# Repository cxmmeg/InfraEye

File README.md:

# InfraEye
**InfraEye** is name for low cost thermal image camera project based on SoC ESP32. 

It uses IR sensor MLX90640B. Image can be viewed by default on web page on web server created by ESP32 or optionally on 2.4'' LCD touch display.

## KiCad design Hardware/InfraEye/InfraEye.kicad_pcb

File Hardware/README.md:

PCB will have ESP8266, Infra sensor, micro USB conector, DC-DC inverter and LCD

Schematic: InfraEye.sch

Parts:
C1, C3: 10nF; C_1206_5MIL_DWS_ISO
C2, C4: 100nF; C_1206_5MIL_DWS_ISO
C5, C6: CP; C_Radial_D5.0mm_H11.0mm_P2.00mm
D1, D2, D3, D4: D; D_1206_3216Metric
D5: D_Zener; D_1206_3216Metric
J1: Conn_01x03_Male; FanPinHeader_1x03_P2.54mm_Vertical
Q1: Q_NPN_BCE; SOT23-3
R1, R2: R; R_1206_5MIL_DWS_ISO
R3: R; R_1206_3216Metric
U1, U4: MLX90640; MLX90614
U2: ESP32-WROOM-32; ESP32-WROOM-32-30pin
U3: TFT_SPI_24_LCD; TFT_LCD_24
U5: LT1129-3.3_SOT223; SOT-223-3_TabPin2

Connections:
+3V3: C1.1, C2.1, C3.1, C4.1, Q1.2 (C), R3.2, U1.2 (VDD), U2.16, U3.1 (VCC), U4.2 (VDD)
+5V: C6.1, U2.1, U5.3
GND: C1.2, C2.2, C3.2, C4.2, C5.2, C6.2, D3.2, D4.1, D5.2, U1.3 (GND), U2.2, U2.17, U3.2 (GND), U4.3 (GND), U5.2
unnamed: C5.1, D1.1, D2.2, D5.1, U5.1
unnamed: D1.2, D3.1, J1.1
unnamed: D2.1, D4.2, J1.2
unnamed: Q1.1 (B), R1.1
unnamed: Q1.3 (E), R2.1
unnamed: R1.2, U2.26
unnamed: R2.2, R3.1, U3.8 (LEDD)
unnamed: U1.1 (SDA), U2.30, U4.1 (SDA)
unnamed: U1.4 (SCL), U2.29, U4.4 (SCL)
unnamed: U2.3, U3.14 (IRQT)
unnamed: U2.4, U3.11 (CST)
unnamed: U2.8, U3.10 (CLKT), U3.18 (SCKC)
unnamed: U2.9, U3.12 (MOSIT), U3.17 (MISOC)
unnamed: U2.10, U3.13 (MISO), U3.16 (MOSIC)
unnamed: U2.11, U3.9 (MISOD)
unnamed: U2.12, U3.15 (CSC)
unnamed: U2.18, U3.3 (CSD)
unnamed: U2.20, U3.4 (RSTD)
unnamed: U2.23, U3.5 (DCD)
unnamed: U2.24, U3.6 (MOSID)
unnamed: U2.25, U3.7 (SCKD)

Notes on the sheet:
Component placement legend: B - Basic components - always populated W - WIFI version L - LCD version A - AC power supply R - Relay O - LCD backlight always on
Power supply

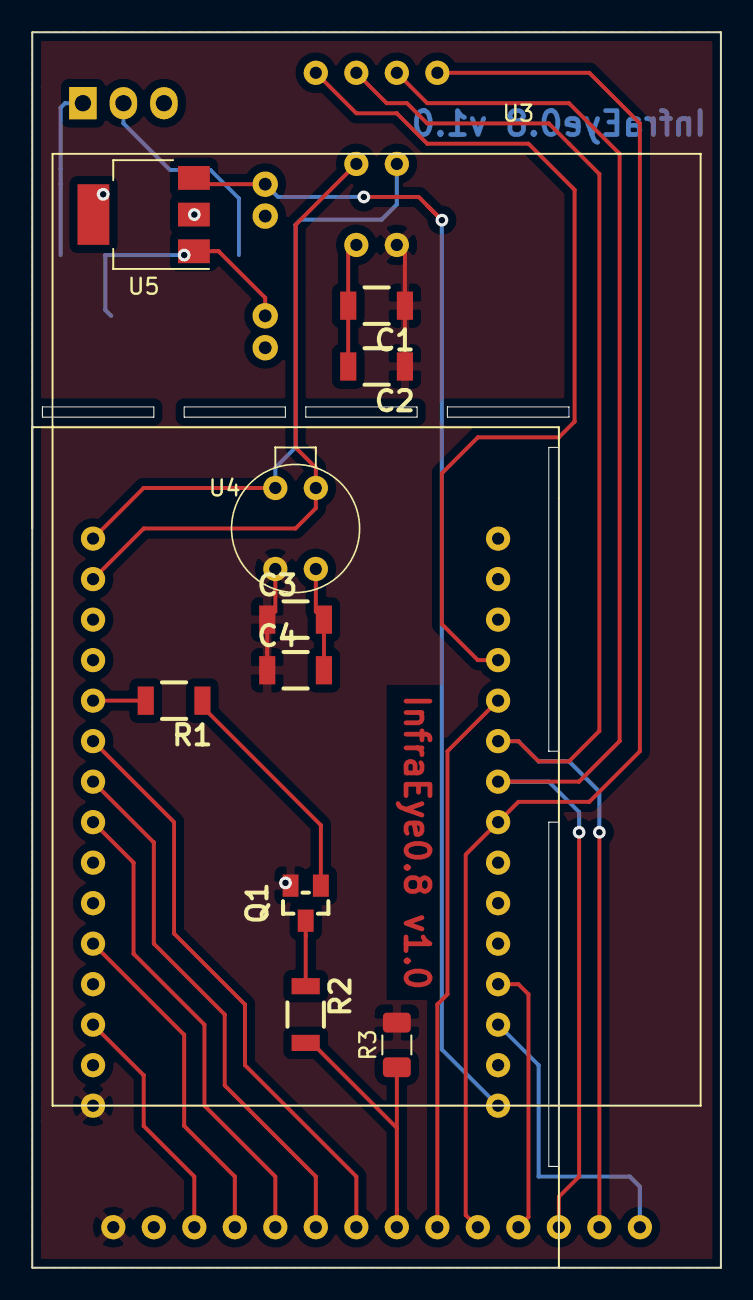
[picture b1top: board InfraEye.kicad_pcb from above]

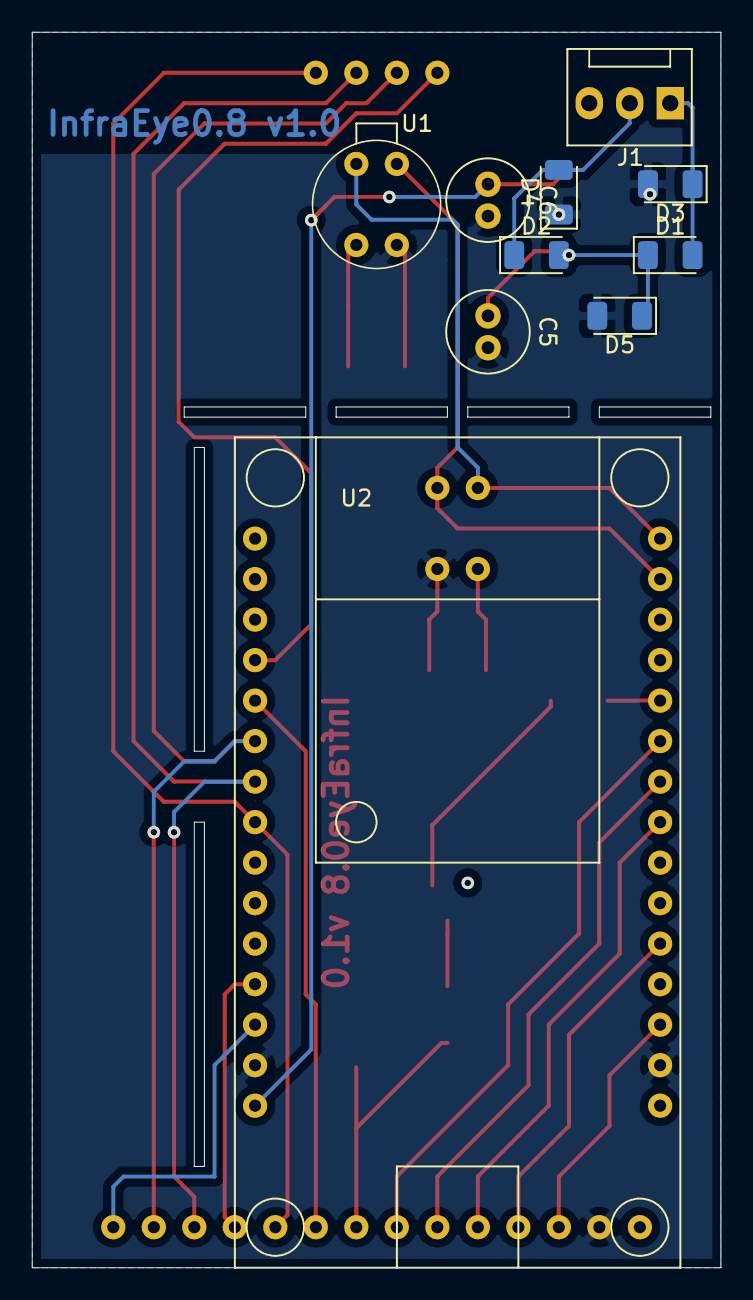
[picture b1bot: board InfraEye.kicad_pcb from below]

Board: 2 copper layers, 43.2 x 77.5 mm, 21 parts (10 on the bottom side), 24 nets.

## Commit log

2018-12-21 Created basic directory structure
2019-01-17 Create 3_Processor
2019-01-17 Create 4_Display
2019-01-17 Create 5_Enclosure
2019-02-10 First draft of Arduino source with I2C communication with IR sensor working
2019-02-10 Fixed problem with buffer length of I2C
    Arduino Wire library is using 32 byte buffer, therefore transaction longer than 32 bytes of usefull data is not possible. Modified to read in chunks not longer tan 32 bytes.
    Added reading of frame from IR sensor. Conversion to temperature added too, but not functional yet.
2019-02-10 Fixed error in I2C driver
    When more than 32 bytes was requested to be read, repeatedly first 32 bytes was read, address was not modified.
2019-02-10 Temperature reading of all pixels implemented
    Both subpages are read now, which allows for calculation of temperatures for all pixels. Correct timing has to be determined as frame rate is currently very low.
2019-02-11 Upscaling algorithm for output data from sensor created in MATLAB.
2019-02-11 Changed mapping of pins so both IR sensor and LCD work together
2019-02-11 Generated C code for upscaling algorithm added.
2019-02-11 Image is displayed on LCD
    32x24 blue coded image is deisplayed on screen
2019-02-11 Generated C code for 4x upscaling algorithm added.
2019-02-12 Generated C code for 2x upscaling algorithm added.
2019-02-12 Added "Iron" IR color palette
    IR color palette implemented
    Automatic range implemented
    Min and Max tepleratures displayed
    Size of image on LCD increased by factor of 8 (huge pixels)
2019-02-15 Improved frame rate to 4FPS
    Changed pattern to interleaved, so only changed pixels can be read efficiently.
    Also only changed pixels are overwritten on LCD.
2019-02-16 Image upscaling algorithm in C added as CodeBlocks project.
2019-02-16 Added document with pinouts and connections
2019-02-17 Image upscaling module added to project.
2019-02-17 Upscaled image displaying added.
2019-02-18 Added upScale sources
    Updated pinout documentaion
    Not a working version
2019-02-18 Revert "Merge branch 'master' of https://github.com/sifosifo/InfraEye"
    This reverts commit 87dfc76a51ad3bbe426f63e0371d4fdf24245b95, reversing
    changes made to 93dad1b0883cd35a66c8071b71e3ff332ed7278e.
2019-02-18 Original and upscaled images on LCD side by side
    Upscaled image on left side and original image at right side of LCD.
    Upscaled image is just black for now for unknown bug.
2019-02-18 Image upscaling fixed.
2019-02-18 Added LIVE_DATA flag
    LIVE_DATA not defined means that temperatures are not taken from IR sensor, but from static array
2019-02-18 Conversion function fixed.
2019-02-19 Beautifull upscaled image at 1,4FPS
2019-02-19 Picture is created only once per full frame
    Due to long calculation times, subPages get lost and picture is distorted.
2019-02-19 GetFrame time reduced by 10ms
    Time reduced from 42ms to 31ms by reading only current subPage.
2019-02-20 Fixed error in GetFrameData
    Error with missing subPages still missing.
    GetFrame now takes 22ms instead of original 42ms
2019-02-21 Fixed problem with loosing subPage 0
    Real FPS is 1 now.
    Changed algorithm to make sure no subPage is lost.
    Image processing is terminated when new subPage is ready for reading resulting in partial image in case that FPS of sensor is too high.
2019-02-21 Image processing is executed during both subPages
    Real FPS is 2
    No buffer is used to make sure that single complete frame is displayed. It is visible.
2019-02-21 Full image is always drawn
    If image processing takes longer than whole frame measurement, image processing is carried out during next frame measurement.
2019-02-22 Created modules
    New module for LCD
    New module for IRsensor
    New config file for whole project
2019-02-22 Added refresh rate of IR sensor into config file
2019-02-22 Reworked time measurement
2019-02-23 Upscaling algorithm optimalized for scaling factor 4.
2019-02-24 Changed temperatures from float to uint16_t
2019-02-24 Fixed type errors
2019-02-24 Look-up tables added.
2019-02-24 Fixed point upscaling algorithm updated. Displaying is not correct - need to be fixed.
2019-02-27 Fixed LIVE_DATA macro, updated documentation - ESP32 added
2019-03-01 LOOK_UP_TABLE_D moved to header file.
2019-04-08 Update Pinounts and connections.docx
    Added pinouts for ESP32 and LCD
2019-04-18 .gitignore added.
2019-04-18 Arduino project deleted from master branch. Arduino source code can be found in dev_arduino branch. New ESP-IDF Toolchain LED blinking application added into master branch.
2019-04-19 Build configuration guide using ESP-IDF toolchain added. Front page README.md updated.
2019-05-01 ESP-IDF display example added.
2019-05-02 app_display module reworked.
2019-05-11 Frequency switched to 240 MHz Moving rectangle application created.
2019-05-11 Removed sdkconfig as it is unique for everybody and having it in repo is causing conflicts.
2019-05-12 Added two tasks. One is currently used just for debugging and the other one makes recalculation for display. In main (idle task) LCD is updated.
2019-05-12 FPS calculation added, not sure if it's calculated correctly.
2019-06-23 For MLX90640 IR sensor added: driver and I2C driver. I2C not working yet.
2019-06-30 I2C driver is initialized and installed. i2c_master_cmd_begin() returns -1 - general I2C error, therefore I2C scan fails.
2019-07-01 I2C scan now finds IR sensor, but timeout is detected ESP_ERR_TIMEOUT 0x107 /*!< Operation timed out */
2019-07-01 I2C scan now finds IR sensor correctly
2019-07-03 I2C read function rewritten from "Arduino to esp_idf", not yet verified if correctly.
2019-07-27 Display colour setting fixed.
2019-07-27 Colour is set according to I2C status.
2019-07-27 Image upscaling module added.
2019-07-28 FPS calculation updated and added into display module. FPS is now 21.
2019-08-26 Updated I2C write. Something is still correct. Value that is read out doesn't match the one that was written. At this point it is not clear if it is issue of reading or writing. Logical analyzator co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
2019-08-27 I2C reading was not correct, repeated start was not present. Both reading and writing seems to be working correctly. Cleanup is needed and debug messages needs to be removed/commented out.
2019-08-28 When using i2c_master_read() MSB, LSB are swapped in every word. When using i2c_master_read_byte() correct order can be selected, but there are delays between bytes read out. For performance purposes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
2019-08-28 Reading of more than single word seems to be correct, but reading many words at once triggers task watchdog.
2019-08-29 When added global u16_pixelValue[768], malloc in app_disp_vInitialize() fails to allocate memory.
2019-11-03 Reduced used LCD screen area
2019-11-23 Read from IR sensor fixed. Temperature calculation added
2020-01-13 Fixed error in coordinate calculation for drawing image from sensor to LCD. Added LSB/MSB switch operation when temperature is converted to color. Fixed color enumerators. Added set pixel function fo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
    Measured data from sensor is displayed on LCD in 300% scale (no filtering, just pixel is 3x3 big).
    FPS is not measured, but is pretty good.
2020-01-15 Added empty module for touchscreen and driver for touchscreen chip XPT2046. Driver needs to be reworked as it is written for different platform.
2020-01-23 Added sources for LCD touch sensor chip (not working currently) Added fixes to sensor reading done by Martin.
2020-01-25 Added footprints for LCD, ESP32 board and IR sensor
2020-01-25 Added footprints
2020-01-25 Fixed footprint for IR sensor (pins were mirrored as if sensor was mounted on other side of PCB)
2020-01-29 Documentation: Updated pictures for ESP32 pinout.
    Configuration:
    SPI pin configuration moved to config.h file.
    Touch:
    Touch sensor moved to second SPI bus (on the same bus as LCD previously), but it's still dissabled as it is causing stability issues.
    Touch sensor reading is working (some data reading from touch chip is working, it reacts to touch, but coordinates are not parsed yet) on LCD SPI bus with LCD disabled (now LCD and touch cannot work 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
2020-01-29 Some pins for touch SPI were in conflict with hardcoded debug pins 26 and 25, so touch SPI pins were moved. It solved stability issue with enabled touch SPI bus initialization.
    Debug pins were temporarily disabled.
    Both LCD and Touch SPI buses are initialized and utilized, LCD works, however no data are coming from touch chip currently.
2020-02-01 PCB: Added second IR sensor - LCD/WIFI version will have IR sensor placed on different places of PCB. SW: Changed pins of SPI buses, LCD moved to VSPI bus and speed increased to 60MHz, touch sensor m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
2020-02-06 Reworked schematics and PCB - signals moved around to minimize signal crossings - not verified on HW if it works with remapped signals as on schematics.
2020-02-15 Updated PCB - added text, finished track routing and fill areas. After verifying that it works as it is on schematics, it will be sent out for review.
2020-02-16 Swapped I2C lines for better trace routing Further improvemets to board, added holes for easier board separation.
2020-02-16 Added AC power supply
2020-02-16 AC power supply added also to PCB
